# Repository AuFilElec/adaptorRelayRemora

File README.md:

#Adaptateur relais pour carte Remora

Cet adaptateur permet de positionner le relais SSR *G3MC-202P-5V* de Omron pour le pilotage du contacteur jour/nuit du ballon d'eau chaude.

En effet, ce relais fonctionne à l'aide d'un triac et possède un snubber (pont RC série) pour piloter des charges inductives, contrairement au précédent relais électro-mécanique.

Pour le bon fonctionnement du relais, il est nécessaire de supprimer la diode *D15* de la carte Remora.
Le seul moyen que j'ai trouvé pour installer cet adaptateur est de le poser avec des headers. Ce ne sera pas très stable pour la soudure, mais cela s'adapte bien et ça passe dans le boîtier Rail DIN.

**PCB**

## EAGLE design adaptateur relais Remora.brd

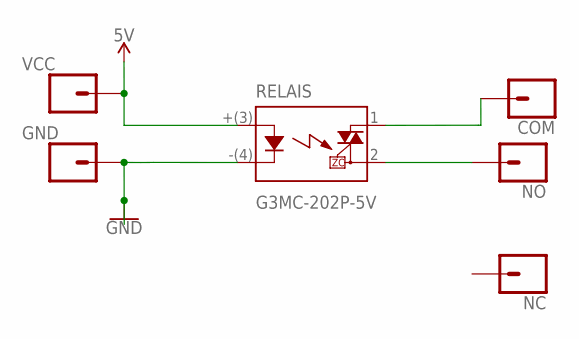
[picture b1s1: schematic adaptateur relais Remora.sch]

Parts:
COM: CONN_01; 1X01
GND: CONN_01; 1X01
NC: CONN_01; 1X01
NO: CONN_01; 1X01
RELAIS: G3MC-202P-5V; SIP-4
VCC: CONN_01; 1X01

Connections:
5V: RELAIS.+(3) (3), VCC.1
GND: GND.1, RELAIS.-(4) (4)
unnamed: COM.1, RELAIS.1
NO: NO.1, RELAIS.2

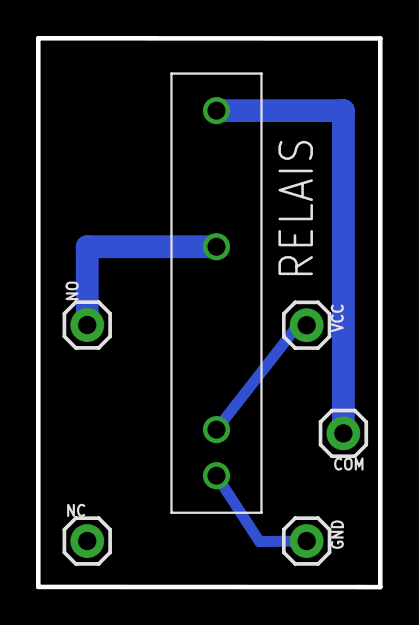
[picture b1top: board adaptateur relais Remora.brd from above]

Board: 2 copper layers, 19.0 x 30.5 mm, 6 parts (0 on the bottom side), 4 nets.

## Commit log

2017-01-03 Ajout du schema, du PCB et d'une image du PCB
2017-01-03 Ajout du README

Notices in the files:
parts and their libraries:
SparkFun-Connectors: Licensing: Creative Commons ShareAlike 4.0 International - https://creativecommons.org/licenses/by-sa/4.0
